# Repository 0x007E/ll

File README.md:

# `LL` - Runnig Light (Lauflicht)

The `ll` project is based on a pcb with a decade counter (`CD4017`) coupled to a timer (`NE555`). The frequency of the timer can be adjusted trough a potentiometer.

| Experience | Level |
|:------------|:-----:|
| Soldering   |  |
| Mechanical  |  |

# Downloads

| Type      | File               | Description              |
|:---------:|:------------------:|:-------------------------|
| Schematic | [pdf](https://github.com/0x007E/ll/releases/latest/download/schematic.pdf) / [cadlab](https://cadlab.io/project/28562/main/files)     | Schematic files          |
| Board     | [pdf](https://github.com/0x007E/ll/releases/latest/download/pcb.pdf) / [cadlab](https://cadlab.io/project/28562/main/files)     | Board file               |
| Drill     | [pdf](https://github.com/0x007E/ll/releases/latest/download/drill.pdf) | Drill file               |
| Gerber    | [zip](https://github.com/0x007E/ll/releases/latest/download/kicad.zip) / [tar](https://github.com/0x007E/ll/releases/latest/download/kicad.tar.gz)                | Gerber/Drill files       |
| Housing, PCB | [zip](https://github.com/0x007E/ll/releases/latest/download/freecad.zip) / [tar](https://github.com/0x007E/ll/releases/latest/download/freecad.tar.gz) | Housing and PCB (STEP) files     |

# Hardware

There are two parts of the hardware. The pcb and the housing of the `LL`. The pcb is created with  `KiCAD` and the housing with `FreeCAD`. All files are built with `github actions` so that they are ready for a production environment. The housing is printed with a 3D-printer (`Dremel 3D40`).

## PCB

The circuit board is populated on one side (Top). The best way for soldering is within a standard soldering system.

### Top Layer

### Bottom Layer

## Mechanical

The housing has a tolerance of `0.2mm` on each side of the case. So the pcb should fit perfectly in the housing. The tolerance can be modified with `FreeCAD` in the `Parameter` Spreadsheet.

### Assembled

#### Exploded

# Additional Information

| Type       | Link               | Description              |
|:----------:|:------------------:|:-------------------------|
| CD4017 | [pdf](https://www.ti.com/lit/ds/symlink/cd4017b.pdf) | Decade counter |
| NE555    | [pdf](https://www.ti.com/lit/ds/symlink/ne555.pdf) | Timer |

---

R. GAECHTER

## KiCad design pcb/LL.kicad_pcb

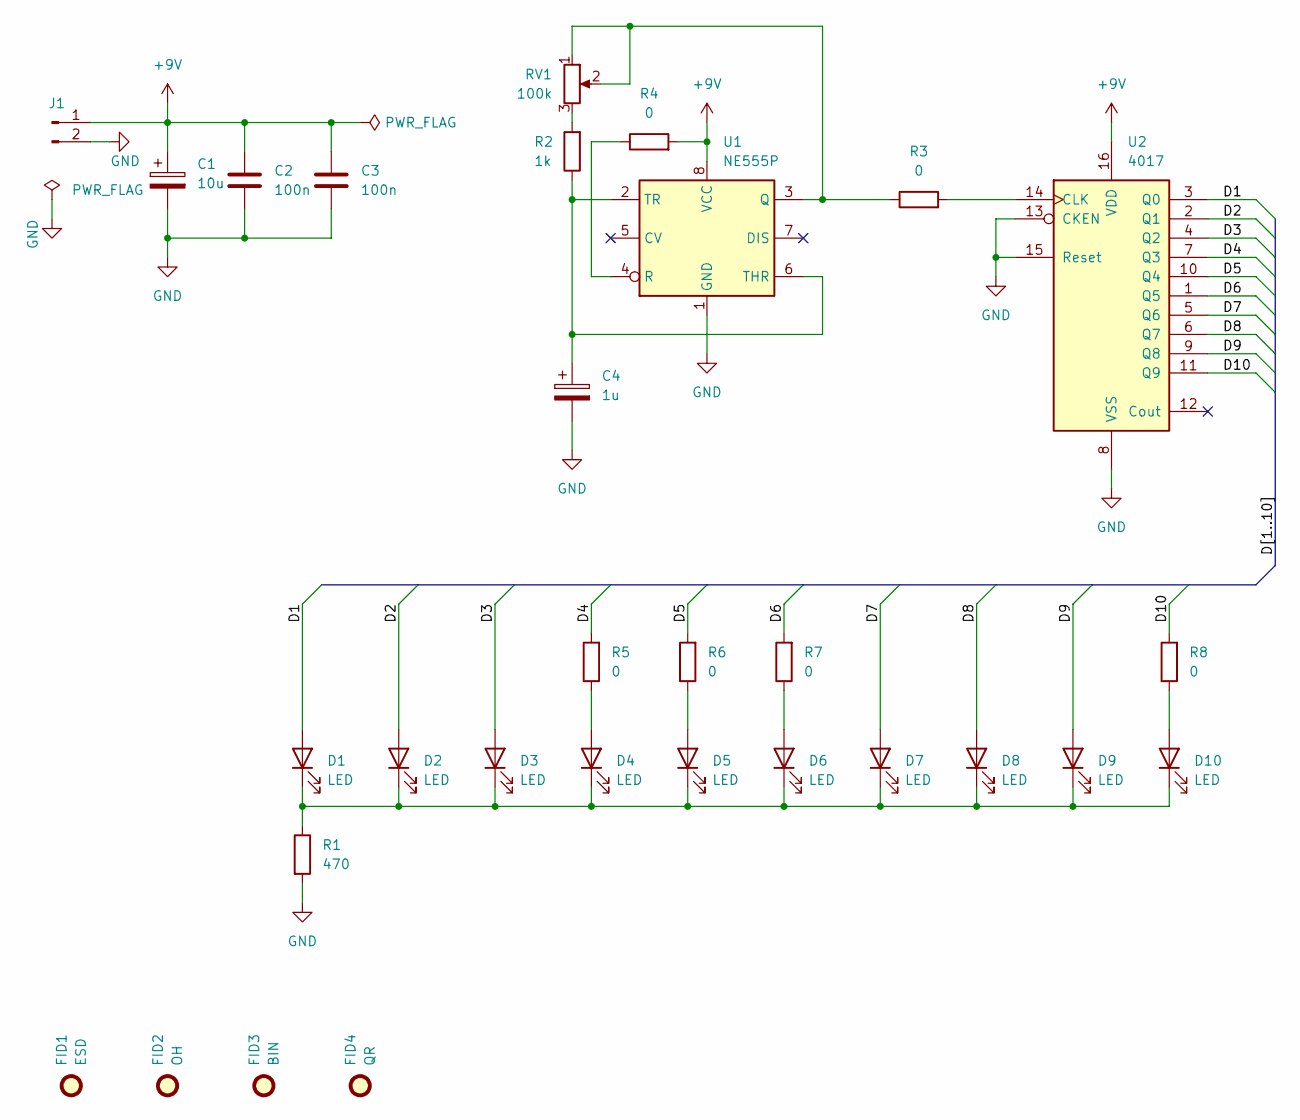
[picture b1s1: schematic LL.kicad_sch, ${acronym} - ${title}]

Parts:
C1: 10u; CP_Radial_D5.0mm_P2.50mm
C2, C3: 100n; C_Disc_D3.8mm_W2.6mm_P2.50mm
C4: 1u; CP_Radial_D5.0mm_P2.50mm
D1, D2, D3, D4, D5, D6, D7, D8, D9, D10: LED; LED_D5.0mm
FID1: ESD; ESD-Logo_6.6x6mm_SilkScreen
FID2: OH; OSHW-Logo2_7.3x6mm_SilkScreen
FID3: BIN; WEEE-Logo_4.2x6mm_SilkScreen
FID4: QR; QR_0x007e
J1: Conn_01x02_Pin; PinSocket_1x02_P2.54mm_Vertical
R1: 470; R_Axial_DIN0207_L6.3mm_D2.5mm_P10.16mm_Horizontal
R2: 1k; R_Axial_DIN0207_L6.3mm_D2.5mm_P10.16mm_Horizontal
R3, R4, R5, R7, R8: 0; R_Axial_DIN0207_L6.3mm_D2.5mm_P10.16mm_Horizontal
R6: 0; R_Axial_DIN0207_L6.3mm_D2.5mm_P15.24mm_Horizontal
RV1: 100k; Potentiometer_Piher_PT-10-V10_Vertical
U1: NE555P; DIP-8_W7.62mm_Socket_LongPads
U2: 4017; DIP-16_W7.62mm_Socket_LongPads

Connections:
+9V: C1.1, C2.1, C3.1, J1.1, R4.2, U1.8 (VCC), U2.16 (VDD)
/D1: D1.2 (A), U2.3 (Q0)
/D2: D2.2 (A), U2.2 (Q1)
/D3: D3.2 (A), U2.4 (Q2)
/D4: R5.2, U2.7 (Q3)
/D5: R6.2, U2.10 (Q4)
/D6: R7.2, U2.1 (Q5)
/D7: D7.2 (A), U2.5 (Q6)
/D8: D8.2 (A), U2.6 (Q7)
/D9: D9.2 (A), U2.9 (Q8)
/D10: R8.2, U2.11 (Q9)
GND: C1.2, C2.2, C3.2, C4.2, J1.2, R1.2, U1.1 (GND), U2.8 (VSS), U2.13 (CKEN), U2.15 (Reset)
unnamed: D1.1 (K), D2.1 (K), D3.1 (K), D4.1 (K), D5.1 (K), D6.1 (K), D7.1 (K), D8.1 (K), D9.1 (K), D10.1 (K), R1.1
unnamed: D4.2 (A), R5.1
unnamed: D5.2 (A), R6.1
unnamed: D6.2 (A), R7.1
unnamed: D10.2 (A), R8.1
unnamed: R2.2, RV1.3
unnamed: R3.1, RV1.1, RV1.2, U1.3 (Q)
unnamed: R4.1, U1.4 (R)
unnamed: C4.1, R2.1, U1.2 (TR), U1.6 (THR)
unnamed: R3.2, U2.14 (CLK)

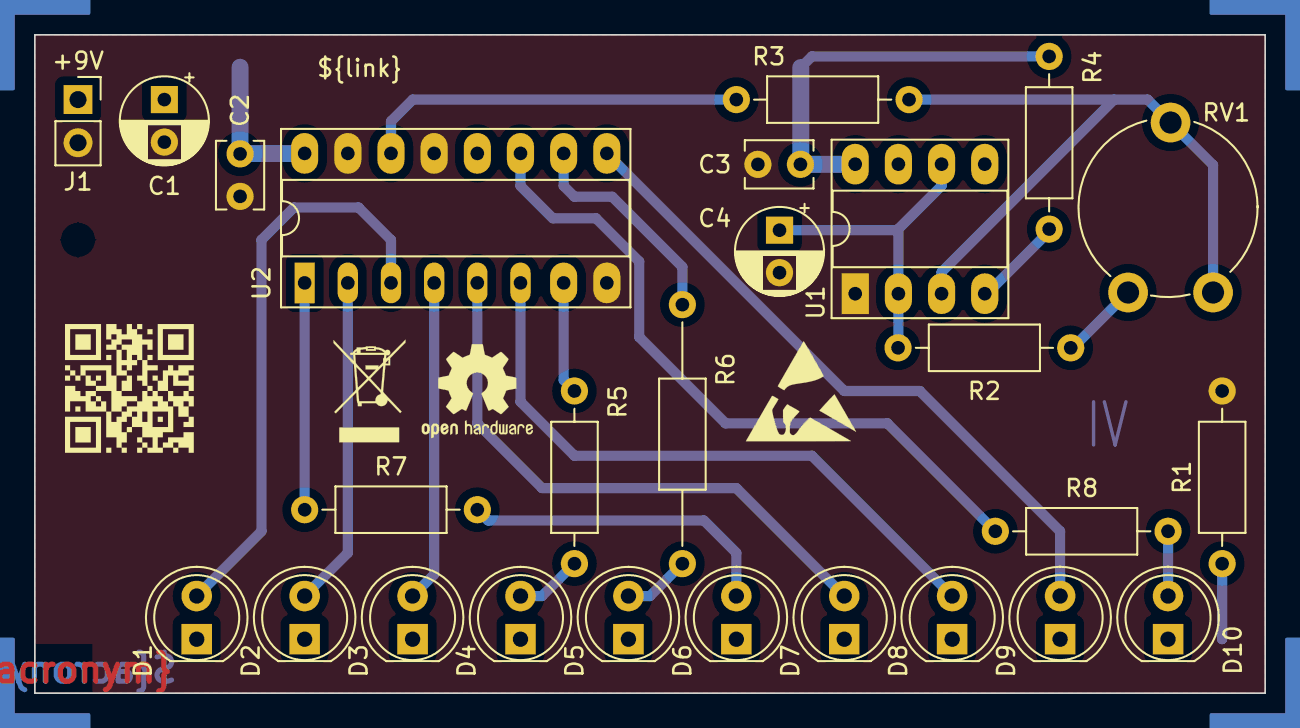
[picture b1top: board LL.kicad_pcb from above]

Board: 2 copper layers, 72.4 x 38.7 mm, 30 parts (0 on the bottom side), 22 nets.

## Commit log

2024-10-15 Fix README
2024-10-15 Update KiBot
2024-10-15 Change date
2024-10-18 Fix typo

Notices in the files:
README.md:
License CC By-NC-SA
parts and their libraries:
license: CC BY-NC-SA 4.0
